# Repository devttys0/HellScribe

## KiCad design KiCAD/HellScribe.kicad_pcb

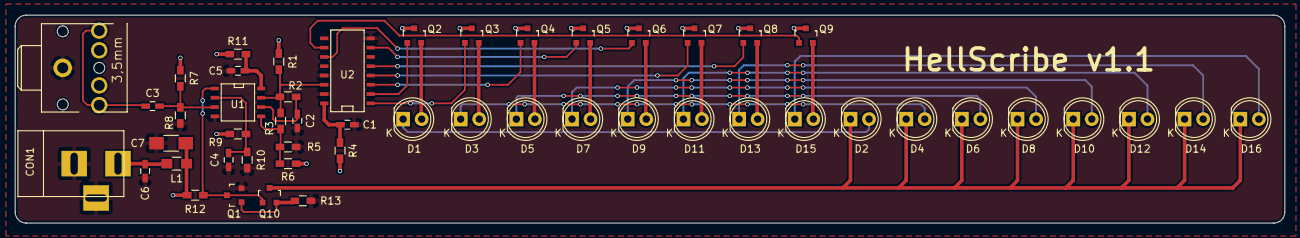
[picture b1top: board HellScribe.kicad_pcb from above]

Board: 2 copper layers, 173.7 x 28.4 mm, 51 parts (0 on the bottom side), 38 nets.

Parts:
C1, C3, C4, C5, C6: 0.1uF; C_0603_HandSoldering
C2: 2.2nF; C_0603_HandSoldering
C7: 10uF; R_1206_HandSoldering
CON1: +12v; BARREL_JACK
D1, D2, D3, D4, D5, D6, D7, D8, D9, D10, D11, D12, D13, D14, D15, D16: LED; LED-5MM
J1: STX-3100-5N; STX3100
L1: 10uH; R_0805_HandSoldering
Q1, Q10: 2N3904; SOT-23
Q2, Q3, Q4, Q5, Q6, Q7, Q8, Q9: Q_PMOS_GSD; SOT-23
R1: 1k; R_0603_HandSoldering
R2: 2.4M; R_0603_HandSoldering
R3, R5, R6, R7, R8, R9: 10k; R_0603_HandSoldering
R4, R11: 100; R_0603_HandSoldering
R10: 11k; R_0603_HandSoldering
R12: 2.2k; R_0603_HandSoldering
R13: 10; R_0603_HandSoldering
U1: LM393; SOIC-8-N
U2: CD4022; SO-16-N

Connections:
+12V: C7.2, L1.1, Q2.3, Q3.3, Q4.3, Q5.3, Q6.3, Q7.3, Q8.3, Q9.3, R1.1, R4.1, R6.2, R7.1, R9.2, R11.1, R12.2
GND: C1.2, C2.1, C4.1, C5.1, C6.1, C7.1, CON1.2, CON1.3, J1.1, Q1.2, R5.1, R8.2, R10.2, R13.2, U1.4, U2.8, U2.13, U2.15
unnamed: C2.2, R2.2, U1.6
unnamed: C3.1, R7.2, R8.1, U1.3
unnamed: C3.2, J1.2, J1.5
unnamed: C4.2, R9.1, R10.1, U1.2
unnamed: C5.2, R11.2, U1.8
unnamed: C6.2, CON1.1, L1.2
unnamed: D1.1, D2.2
unnamed: D1.2, Q2.2
unnamed: D3.1, D4.2
unnamed: D3.2, Q3.2
unnamed: D5.1, D6.2
unnamed: D5.2, Q4.2
unnamed: D7.1, D8.2
unnamed: D7.2, Q5.2
unnamed: D9.2, Q6.2
unnamed: D2.1, D4.1, D6.1, D8.1, D10.1, D12.1, D14.1, D16.1, Q10.3
unnamed: D9.1, D10.2
unnamed: D11.1, D12.2
unnamed: D11.2, Q7.2
unnamed: D13.1, D14.2
unnamed: D13.2, Q8.2
unnamed: D15.1, D16.2
unnamed: D15.2, Q9.2
unnamed: Q1.1, Q10.2, R13.1
unnamed: Q1.3, Q10.1, R12.1, U1.1
unnamed: Q2.1, U2.2
unnamed: Q3.1, U2.1
unnamed: Q4.1, U2.3
unnamed: Q5.1, U2.7
unnamed: Q6.1, U2.11
unnamed: Q7.1, U2.4
unnamed: Q8.1, U2.5
unnamed: Q9.1, U2.10
unnamed: R1.2, R2.1, R3.2, U1.7, U2.14
unnamed: R3.1, R5.2, R6.1, U1.5
VDD: C1.1, R4.2, U2.16

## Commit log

2016-08-27 Initial check in
2016-08-27 Added gerber files
2016-08-27 Deleted .DS_Store files
2016-08-28 Improved PS filtering, updated version to v1.1
2016-08-28 Added Digikey BOM file
2016-09-17 Fixed PMOS orientation.
2016-09-18 Updated Gerbers
2016-09-21 Updated C7
2016-10-04 Changed R1 BOM from 0402 to 0603.
